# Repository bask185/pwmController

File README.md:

# general purpose IO module with PWM/DCC controller

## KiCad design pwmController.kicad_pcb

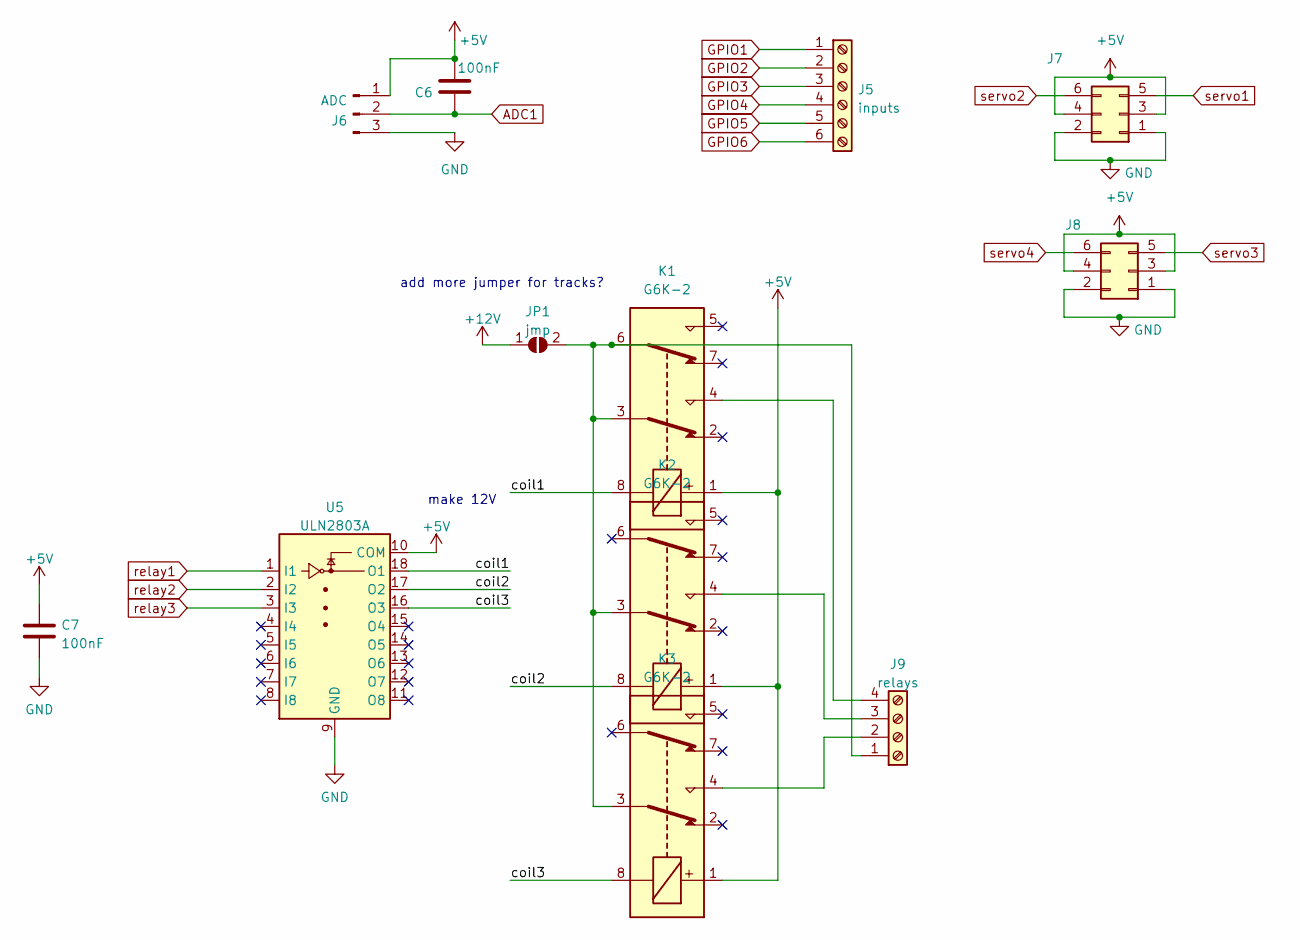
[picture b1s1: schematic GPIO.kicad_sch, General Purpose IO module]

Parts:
C6, C7: 100nF; C_0805_2012Metric
J5: inputs; TerminalBlock_Phoenix_MPT-0,5-8-2.54_1x06_P2.54mm_Horizontal
J6: ADC; PinHeader_1x03_P2.54mm_Vertical
J7, J8: Conn_02x03_Odd_Even; PinHeader_2x03_P2.54mm_Vertical_SMD
J9: relays; TerminalBlock_Phoenix_MKDS-1,5-4-5.08_1x04_P5.08mm_Horizont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
JP1: jmp; SolderJumper-2_P1.3mm_Open_RoundedPad1.0x1.5mm
K1, K2, K3: G6K-2; Relay_DPDT_Omron_G6K-2F-Y; JLCPCB Part# C47190
U5: ULN2803A; SOIC-18W_7.5x11.6mm_P1.27mm

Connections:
+5V: C6.2, C7.1, J6.1, J7.3, J7.4, J8.3, J8.4, K1.1, K2.1, K3.1, U5.10 (COM); also elsewhere on the board
+12V: JP1.1 (A); also elsewhere on the board
/GPIO/coil1: K1.8, U5.18 (O1)
/GPIO/coil2: K2.8, U5.17 (O2)
/GPIO/coil3: K3.8, U5.16 (O3)
ADC1: C6.1, J6.2; also elsewhere on the board
GND: C7.2, J6.3, J7.1, J7.2, J8.1, J8.2, U5.9 (GND); also elsewhere on the board
unnamed: J9.2, K3.4
unnamed: J9.3, K2.4
unnamed: J9.4, K1.4
unnamed: J9.1, JP1.2 (B), K1.3, K1.6, K2.3, K3.3
relay1: U5.1 (I1); also elsewhere on the board
relay2: U5.2 (I2); also elsewhere on the board
relay3: U5.3 (I3); also elsewhere on the board
servo1: J7.5; also elsewhere on the board
servo2: J7.6; also elsewhere on the board
servo3: J8.5; also elsewhere on the board
servo4: J8.6; also elsewhere on the board

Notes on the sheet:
make 12V
add more jumper for tracks?

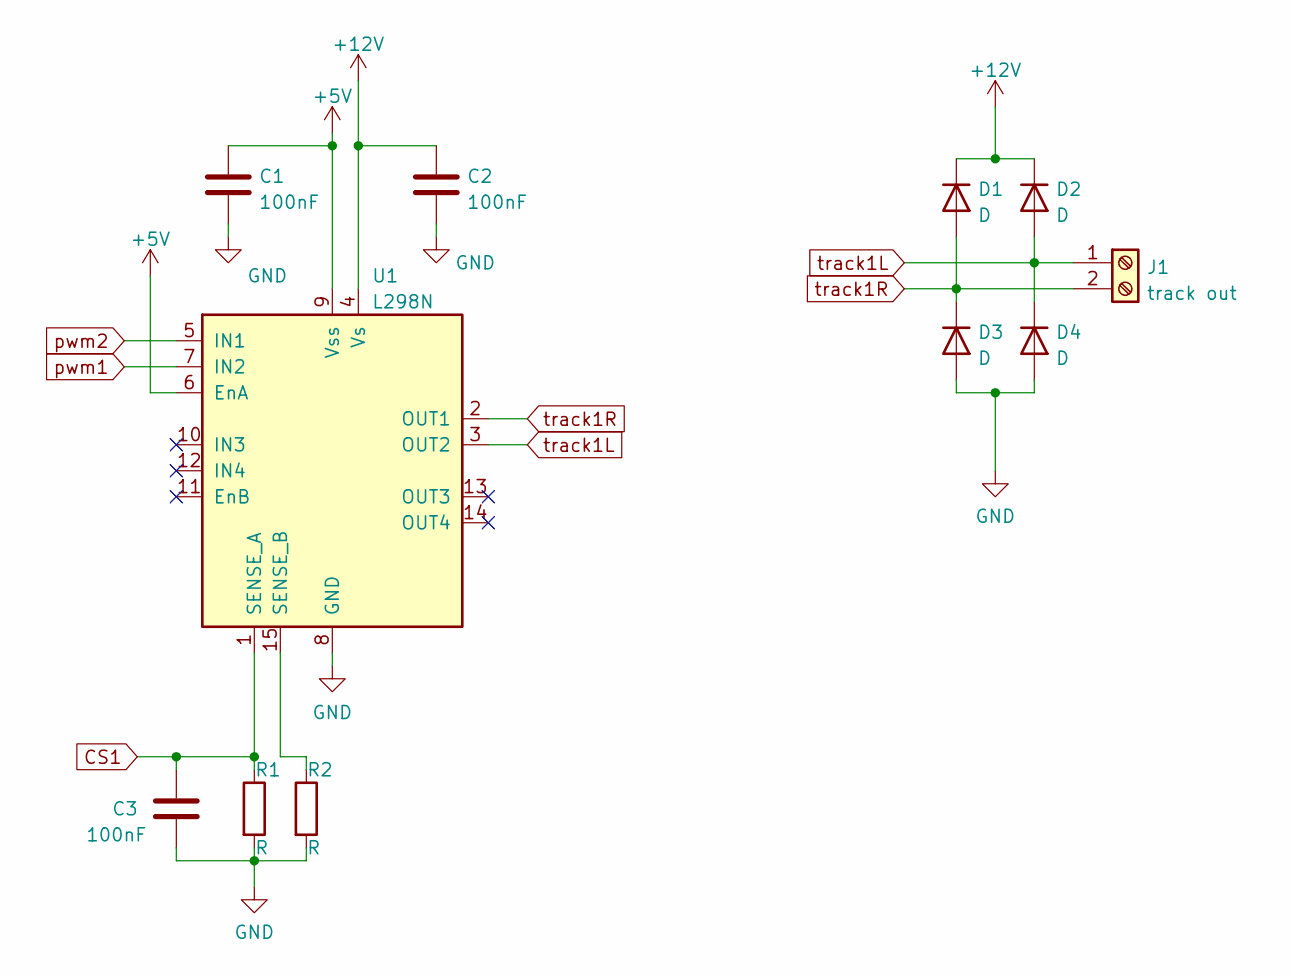
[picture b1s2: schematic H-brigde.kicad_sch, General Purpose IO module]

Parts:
C1, C2, C3: 100nF; C_0805_2012Metric
D1, D2, D3, D4: D; D_1206_3216Metric
J1: track out; TerminalBlock_Phoenix_MKDS-1,5-2-5.08_1x02_P5.08mm_Horizont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
R1, R2: R; R_1206_3216Metric_Pad1.30x1.75mm_HandSolder; JLCPCB Part# C25334
U1: L298N; TO-220-15_P2.54x2.54mm_StaggerOdd_Lead4.58mm_Vertical

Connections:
+5V: C1.1, U1.6 (EnA), U1.9 (Vss); also elsewhere on the board
+12V: C2.1, D1.1 (K), D2.1 (K), U1.4 (Vs); also elsewhere on the board
CS1: C3.2, R1.1, U1.1 (SENSE_A); also elsewhere on the board
GND: C1.2, C2.2, C3.1, D3.2 (A), D4.2 (A), R1.2, R2.2, U1.8 (GND); also elsewhere on the board
unnamed: R2.1, U1.15 (SENSE_B)
pwm1: U1.7 (IN2); also elsewhere on the board
pwm2: U1.5 (IN1); also elsewhere on the board
track1L: D2.2 (A), D4.1 (K), J1.1, U1.3 (OUT2)
track1R: D1.2 (A), D3.1 (K), J1.2, U1.2 (OUT1)

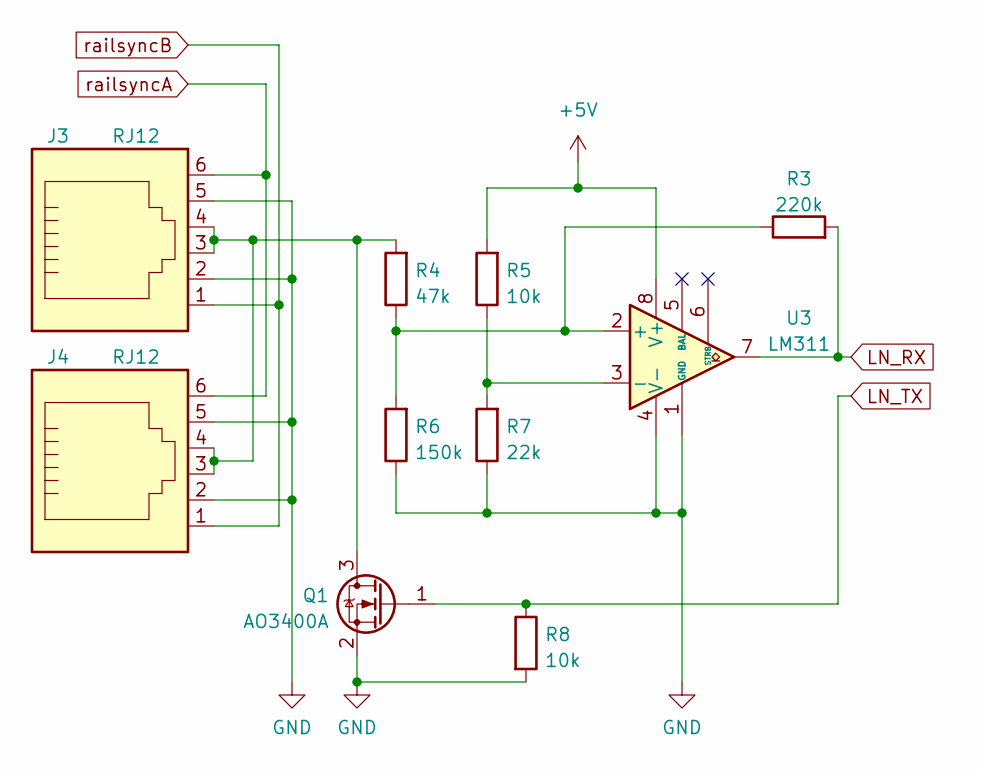
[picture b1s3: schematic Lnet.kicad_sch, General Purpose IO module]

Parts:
J3, J4: RJ12; RJ25_Wayconn_MJEA-660X1_Horizontal; JLCPCB Part# C77859
Q1: AO3400A; SOT-23; JLCPCB Part# C20917
R3: 220k; R_0805_2012Metric_Pad1.20x1.40mm_HandSolder
R4: 47k; R_0805_2012Metric_Pad1.20x1.40mm_HandSolder
R5, R8: 10k; R_0805_2012Metric_Pad1.20x1.40mm_HandSolder
R6: 150k; R_0805_2012Metric_Pad1.20x1.40mm_HandSolder
R7: 22k; R_0805_2012Metric_Pad1.20x1.40mm_HandSolder
U3: LM311; SOP-8_3.9x4.9mm_P1.27mm; JLCPCB Part# C434495

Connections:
+5V: R5.2, U3.8 (V+); also elsewhere on the board
GND: J3.2, J3.5, J4.2, J4.5, Q1.2 (S), R6.1, R7.1, R8.2, U3.1 (GND), U3.4 (V-); also elsewhere on the board
LN_RX: R3.2, U3.7; also elsewhere on the board
LN_TX: Q1.1 (G), R8.1; also elsewhere on the board
unnamed: J3.3, J3.4, J4.3, J4.4, Q1.3 (D), R4.2
unnamed: R3.1, R4.1, R6.2, U3.2 (+)
unnamed: R5.1, R7.2, U3.3 (-)
railsyncA: J3.6, J4.6; also elsewhere on the board
railsyncB: J3.1, J4.1; also elsewhere on the board

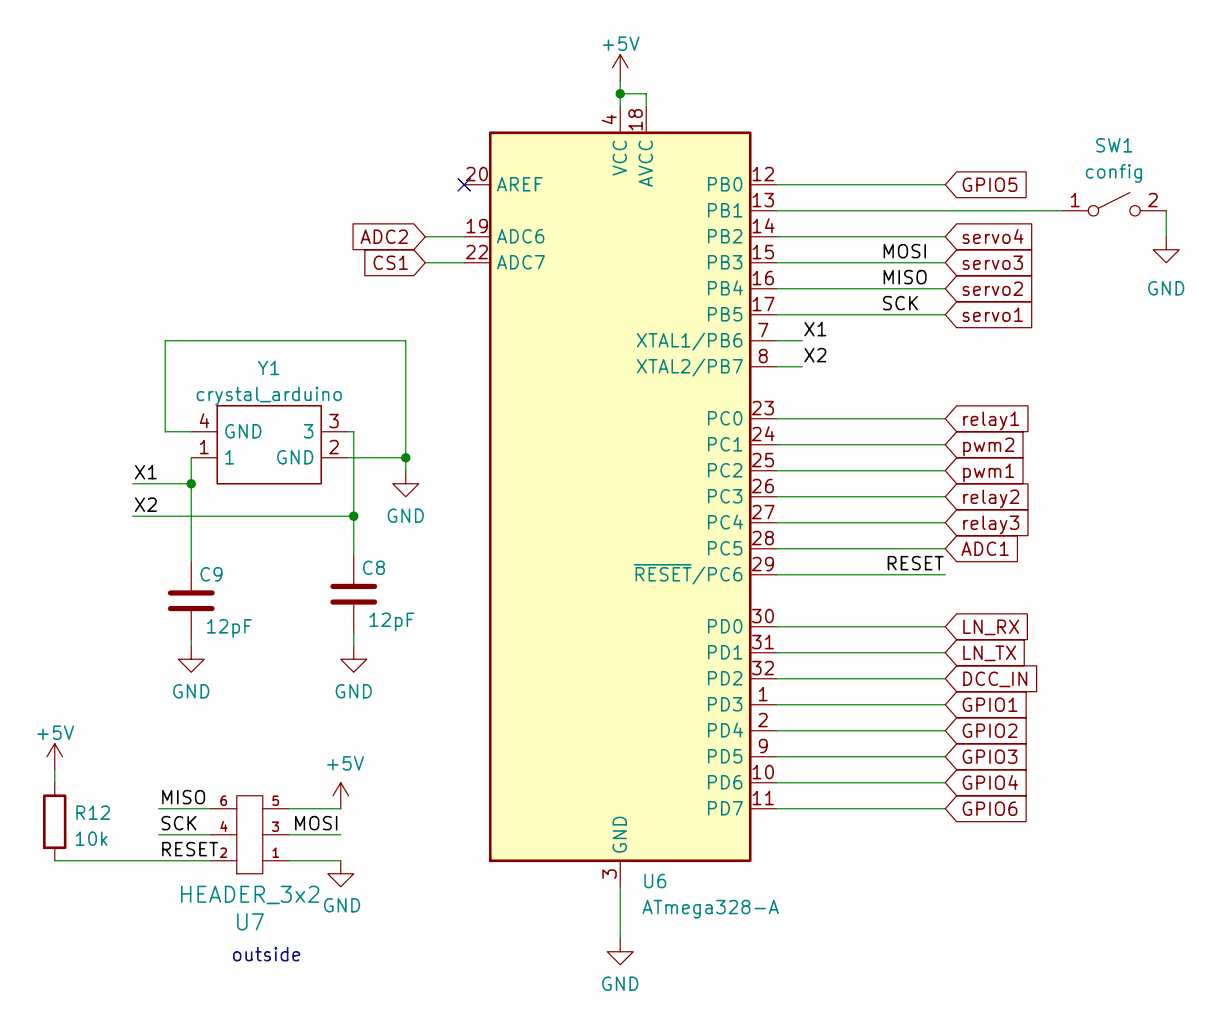
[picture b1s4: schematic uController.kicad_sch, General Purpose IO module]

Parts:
C8, C9: 12pF; C_0603_1608Metric_Pad1.08x0.95mm_HandSolder; JLCPCB Part# C38523
R12: 10k; R_0603_1608Metric_Pad0.98x0.95mm_HandSolder; JLCPCB Part# C25804
SW1: config; SW_SPST_SKQG_WithStem; JLCPCB Part# C318884
U6: ATmega328-A; TQFP-32_7x7mm_P0.8mm; JLCPCB Part# C14877
U7: HEADER_3x2; PinSocket_2x03_P1.27mm_Vertical
Y1: crystal_arduino; JLCPCB Part# C13738

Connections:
+5V: R12.1, U6.4 (VCC), U6.6 (VCC), U6.18 (AVCC), U7.5; also elsewhere on the board
/uController/RESET: R12.2, U6.29 (~RESET/PC6), U7.2
/uController/X1: C9.2, U6.7 (XTAL1/PB6), Y1.1
/uController/X2: C8.2, U6.8 (XTAL2/PB7), Y1.3
ADC1: U6.28 (PC5); also elsewhere on the board
ADC2: U6.19 (ADC6)
CS1: U6.22 (ADC7); also elsewhere on the board
DCC_IN: U6.32 (PD2); also elsewhere on the board
GND: C8.1, C9.1, SW1.2 (B), U6.3 (GND), U6.5 (GND), U6.21 (GND), U7.1, Y1.2 (GND), Y1.4 (GND); also elsewhere on the board
GPIO1: U6.1 (PD3)
GPIO2: U6.2 (PD4)
GPIO3: U6.9 (PD5)
GPIO4: U6.10 (PD6)
GPIO5: U6.12 (PB0)
GPIO6: U6.11 (PD7)
LN_RX: U6.30 (PD0); also elsewhere on the board
LN_TX: U6.31 (PD1); also elsewhere on the board
unnamed: SW1.1 (A), U6.13 (PB1)
pwm1: U6.25 (PC2); also elsewhere on the board
pwm2: U6.24 (PC1); also elsewhere on the board
relay1: U6.23 (PC0); also elsewhere on the board
relay2: U6.26 (PC3); also elsewhere on the board
relay3: U6.27 (PC4); also elsewhere on the board
servo1: U6.17 (PB5), U7.4; also elsewhere on the board
servo2: U6.16 (PB4), U7.6; also elsewhere on the board
servo3: U6.15 (PB3), U7.3; also elsewhere on the board
servo4: U6.14 (PB2); also elsewhere on the board

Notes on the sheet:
outside

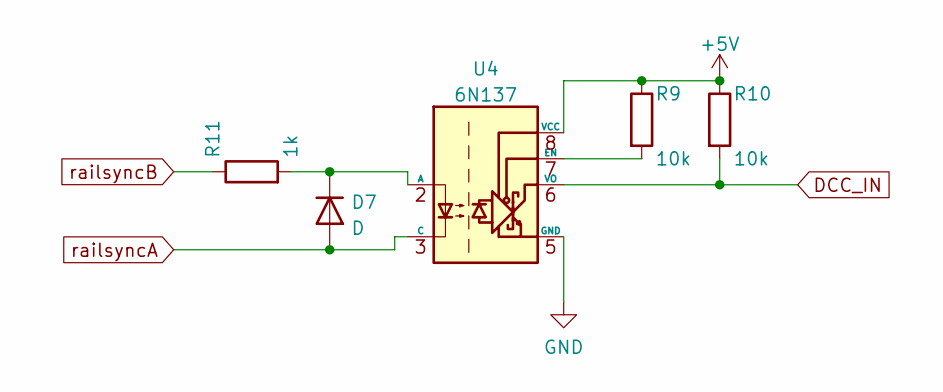
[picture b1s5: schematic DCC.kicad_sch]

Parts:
D7: D; D_1206_3216Metric
R9, R10: 10k; R_0805_2012Metric_Pad1.20x1.40mm_HandSolder; JLCPCB Part# C17414
R11: 1k; R_0805_2012Metric_Pad1.20x1.40mm_HandSolder; JLCPCB Part# C17513
U4: 6N137; SOP-8_6.62x9.15mm_P2.54mm; JLCPCB Part# C110020

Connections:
+5V: R9.1, R10.1, U4.8 (VCC); also elsewhere on the board
DCC_IN: R10.2, U4.6 (VO); also elsewhere on the board
GND: U4.5 (GND); also elsewhere on the board
unnamed: D7.1 (K), R11.2, U4.2 (A)
unnamed: R9.2, U4.7 (EN)
railsyncA: D7.2 (A), U4.3 (C); also elsewhere on the board
railsyncB: R11.1; also elsewhere on the board

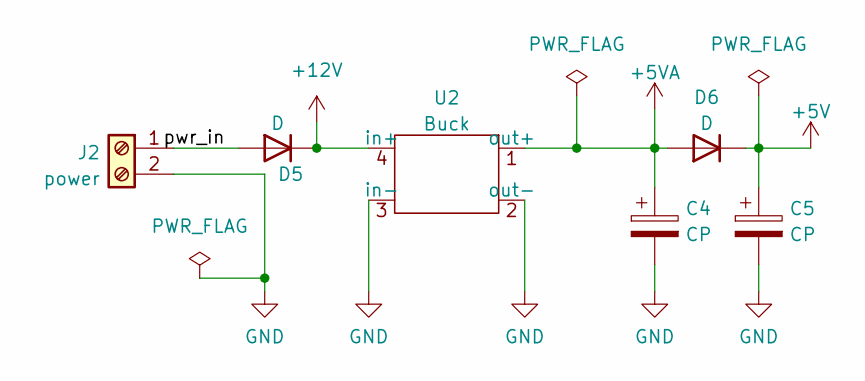
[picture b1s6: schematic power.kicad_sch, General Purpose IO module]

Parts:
C4, C5: CP; CP_Elec_6.3x7.7; JLCPCB Part# C125975
D5, D6: D; D_1206_3216Metric
J2: power; TerminalBlock_Phoenix_MKDS-1,5-2-5.08_1x02_P5.08mm_Horizont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
U2: Buck

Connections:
+5V: C5.1, D6.1 (K); also elsewhere on the board
+5VA: C4.1, D6.2 (A), U2.1 (out+)
+12V: D5.1 (K), U2.4 (in+); also elsewhere on the board
/power/pwr_in: D5.2 (A), J2.1
GND: C4.2, C5.2, J2.2, U2.2 (out-), U2.3 (in-); also elsewhere on the board

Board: 2 copper layers, 50 parts (1 on the bottom side), 40 nets, no tracks yet.

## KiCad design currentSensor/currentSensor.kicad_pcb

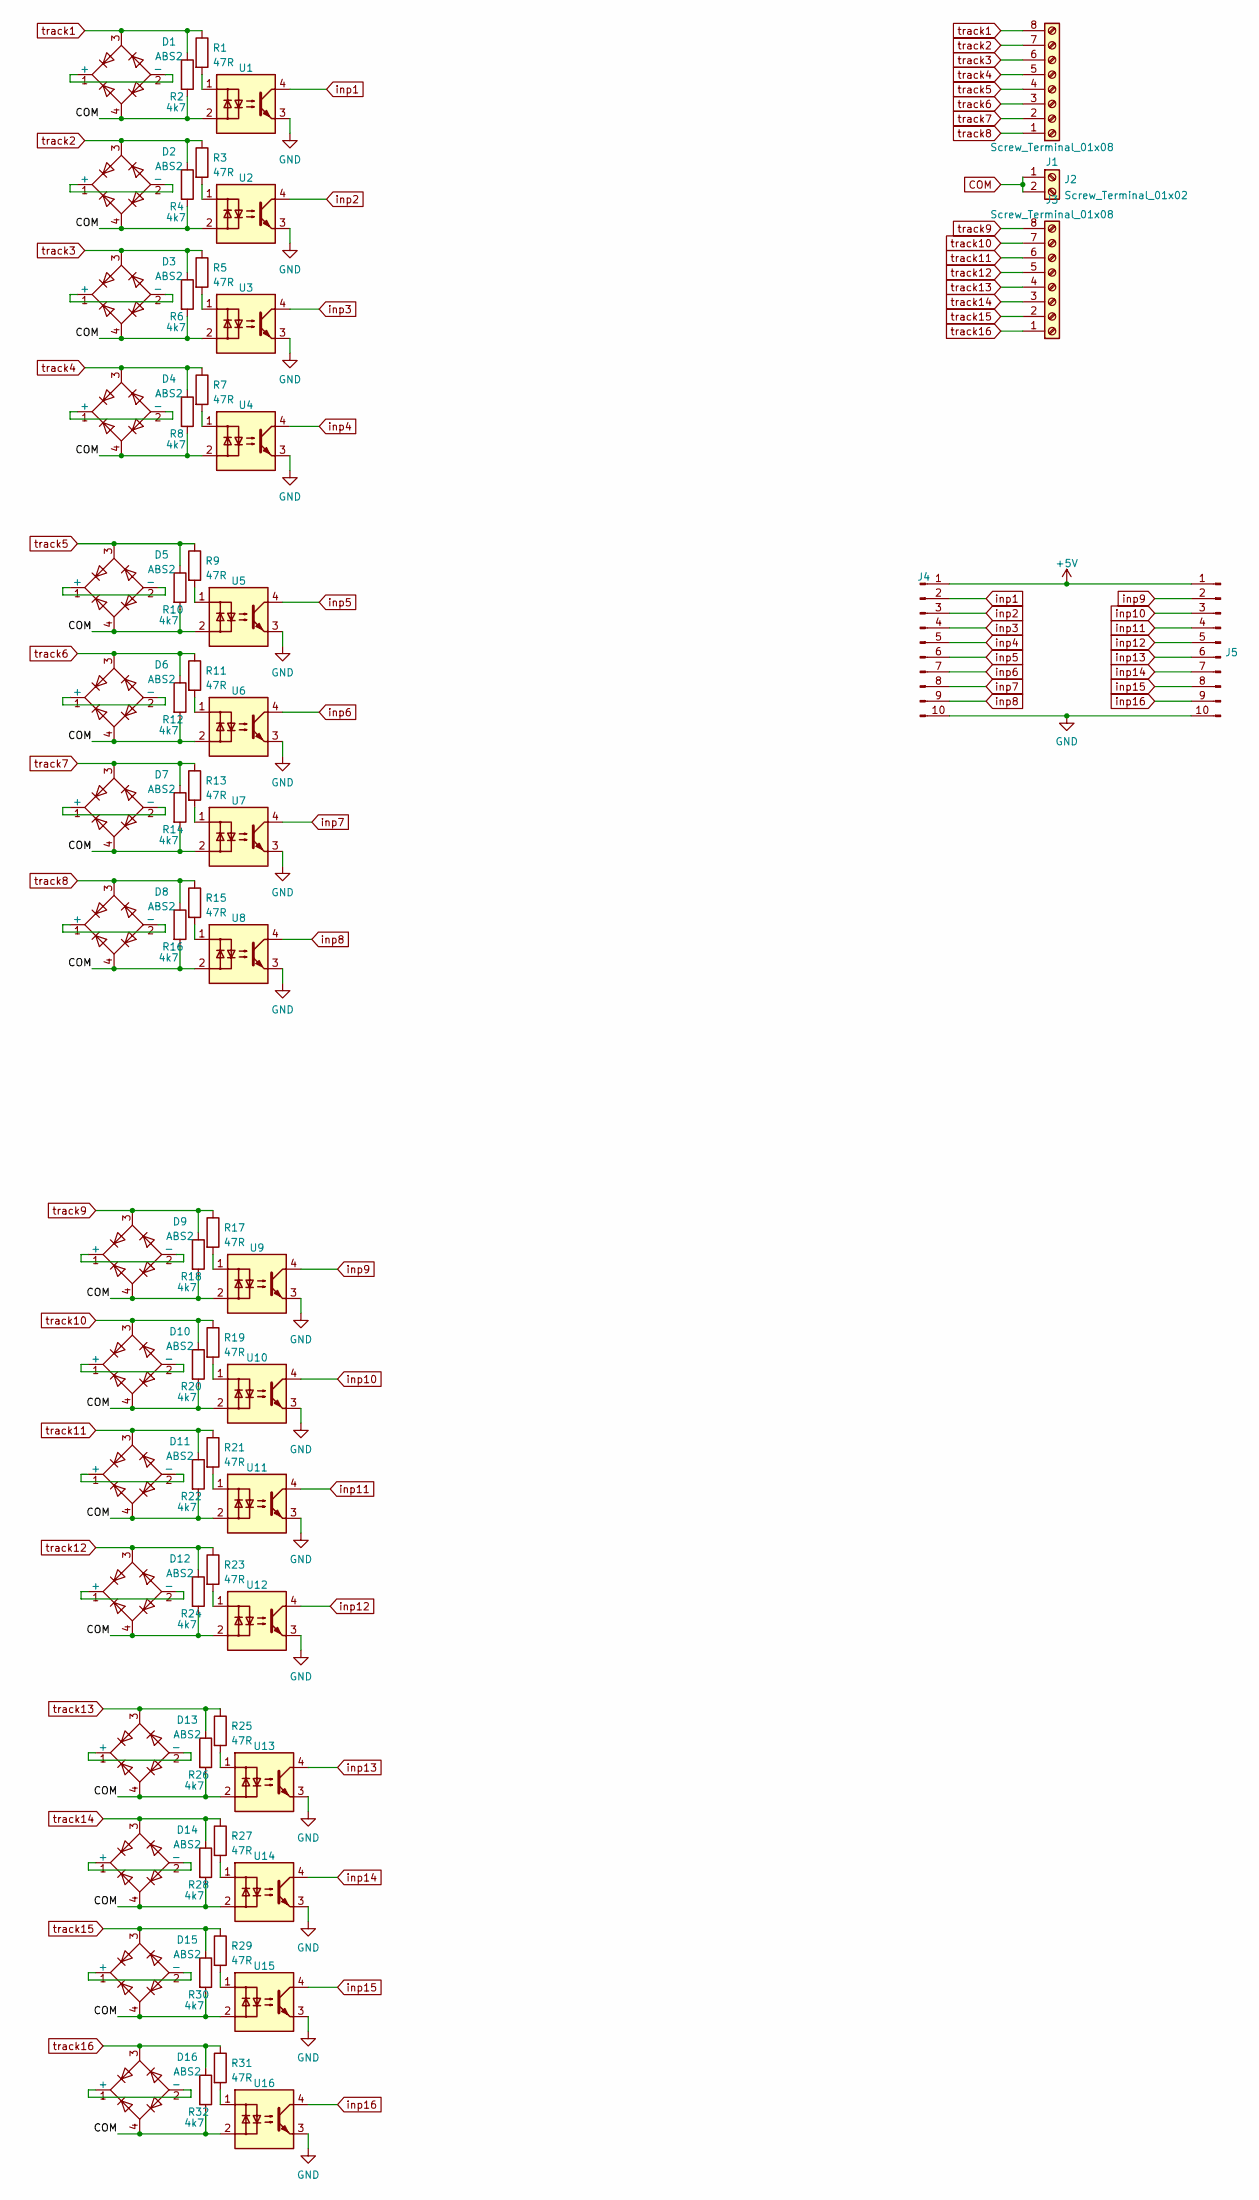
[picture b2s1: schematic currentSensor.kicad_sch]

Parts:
D1, D2, D3, D4, D5, D6, D7, D8, D9, D10, D11, D12, D13, D14, D15, D16: ABS2; Diode_Bridge_Diotec_ABS; JLCPCB Part# C123897
J1, J3: Screw_Terminal_01x08; TerminalBlock_Phoenix_MKDS-1,5-8-5.08_1x08_P5.08mm_Horizont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
J2: Screw_Terminal_01x02; TerminalBlock_Phoenix_MKDS-1,5-2-5.08_1x02_P5.08mm_Horizont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
J4, J5: Conn_01x10_Male; PinHeader_1x10_P2.54mm_Horizontal
R1, R3, R5, R7, R9, R11, R13, R15, R17, R19, R21, R23, R25, R27, R29, R31: 47R; R_0805_2012Metric_Pad1.20x1.40mm_HandSolder; JLCPCB Part# C17714
R2, R4, R6, R8, R10, R12, R14, R16, R18, R20, R22, R24, R26, R28, R30, R32: 4k7; R_0805_2012Metric_Pad1.20x1.40mm_HandSolder; JLCPCB Part# C17673
U1, U2, U3, U4, U5, U6, U7, U8, U9, U10, U11, U12, U13, U14, U15, U16: SFH6206-2T; SMDIP-4_W9.53mm_Clearance8mm; JLCPCB Part# C143678

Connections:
+5V: J4.1, J5.1
COM: D1.4, D2.4, D3.4, D4.4, D5.4, D6.4, D7.4, D8.4, D9.4, D10.4, D11.4, D12.4, D13.4, D14.4, D15.4, D16.4, J2.1, J2.2, R2.2, R4.2, R6.2, R8.2, R10.2, R12.2, R14.2, R16.2, R18.2, R20.2, R22.2, R24.2, R26.2, R28.2, R30.2, R32.2, U1.2, U2.2, U3.2, U4.2, U5.2, U6.2, U7.2, U8.2, U9.2, U10.2, U11.2, U12.2, U13.2, U14.2, U15.2, U16.2
GND: J4.10, J5.10, U1.3, U2.3, U3.3, U4.3, U5.3, U6.3, U7.3, U8.3, U9.3, U10.3, U11.3, U12.3, U13.3, U14.3, U15.3, U16.3
unnamed: D1.1 (+), D1.2 (-)
unnamed: D2.1 (+), D2.2 (-)
unnamed: D3.1 (+), D3.2 (-)
unnamed: D4.1 (+), D4.2 (-)
unnamed: D5.1 (+), D5.2 (-)
unnamed: D6.1 (+), D6.2 (-)
unnamed: D7.1 (+), D7.2 (-)
unnamed: D8.1 (+), D8.2 (-)
unnamed: D9.1 (+), D9.2 (-)
unnamed: D10.1 (+), D10.2 (-)
unnamed: D11.1 (+), D11.2 (-)
unnamed: D12.1 (+), D12.2 (-)
unnamed: D13.1 (+), D13.2 (-)
unnamed: D14.1 (+), D14.2 (-)
unnamed: D15.1 (+), D15.2 (-)
unnamed: D16.1 (+), D16.2 (-)
unnamed: R1.2, U1.1
unnamed: R3.2, U2.1
unnamed: R5.2, U3.1
unnamed: R7.2, U4.1
unnamed: R9.2, U5.1
unnamed: R11.2, U6.1
unnamed: R13.2, U7.1
unnamed: R15.2, U8.1
unnamed: R17.2, U9.1
unnamed: R19.2, U10.1
unnamed: R21.2, U11.1
unnamed: R23.2, U12.1
unnamed: R25.2, U13.1
unnamed: R27.2, U14.1
unnamed: R29.2, U15.1
unnamed: R31.2, U16.1
inp1: J4.2, U1.4
inp2: J4.3, U2.4
inp3: J4.4, U3.4
inp4: J4.5, U4.4
inp5: J4.6, U5.4
inp6: J4.7, U6.4
inp7: J4.8, U7.4
inp8: J4.9, U8.4
inp9: J5.2, U9.4
inp10: J5.3, U10.4
inp11: J5.4, U11.4
inp12: J5.5, U12.4
inp13: J5.6, U13.4
inp14: J5.7, U14.4
inp15: J5.8, U15.4
inp16: J5.9, U16.4
track1: D1.3, J1.8, R1.1, R2.1
track2: D2.3, J1.7, R3.1, R4.1
track3: D3.3, J1.6, R5.1, R6.1
track4: D4.3, J1.5, R7.1, R8.1
track5: D5.3, J1.4, R9.1, R10.1
track6: D6.3, J1.3, R11.1, R12.1
track7: D7.3, J1.2, R13.1, R14.1
track8: D8.3, J1.1, R15.1, R16.1
track9: D9.3, J3.8, R17.1, R18.1
track10: D10.3, J3.7, R19.1, R20.1
track11: D11.3, J3.6, R21.1, R22.1
track12: D12.3, J3.5, R23.1, R24.1
track13: D13.3, J3.4, R25.1, R26.1
track14: D14.3, J3.3, R27.1, R28.1
track15: D15.3, J3.2, R29.1, R30.1
track16: D16.3, J3.1, R31.1, R32.1

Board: 2 copper layers, 69 parts (0 on the bottom side), 67 nets, no tracks yet.

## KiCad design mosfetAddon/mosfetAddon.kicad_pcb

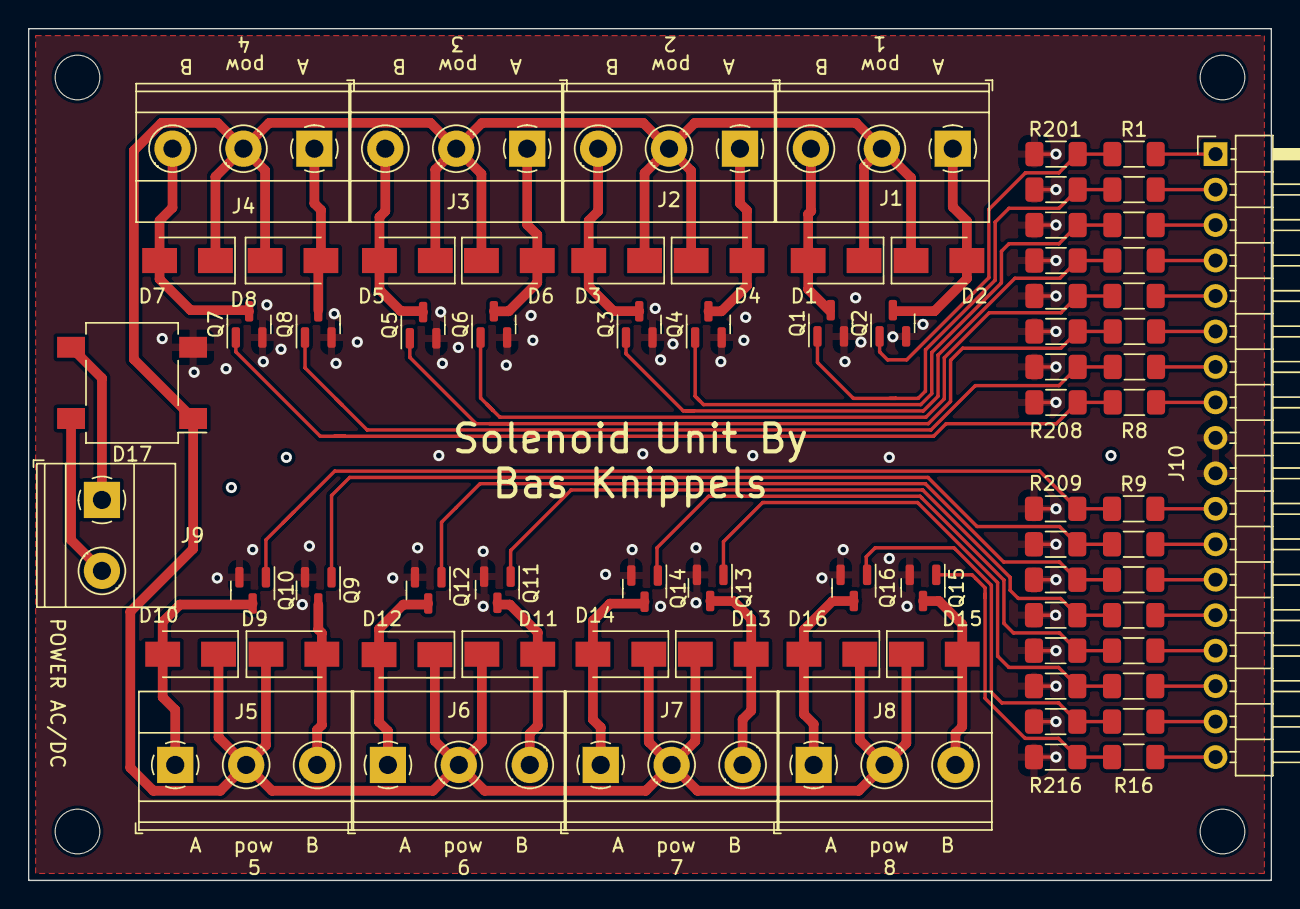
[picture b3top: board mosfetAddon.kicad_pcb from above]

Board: 2 copper layers, 89.0 x 61.0 mm, 75 parts (0 on the bottom side), 52 nets.

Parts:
D1, D2, D3, D4, D5, D6, D7, D8, D9, D10, D11, D12, D13, D14, D15, D16: D; D_SMA
D17: D_Bridge_+-AA; Diode_Bridge_Diotec_SO-DIL-Slim
J1, J2, J3, J4, J5, J6, J7, J8: coil; TerminalBlock_Phoenix_MKDS-1,5-3-5.08_1x03_P5.08mm_Horizont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
J9: pow; TerminalBlock_Phoenix_MKDS-1,5-2-5.08_1x02_P5.08mm_Horizont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
J10: Conn_01x18_Male; PinHeader_1x18_P2.54mm_Horizontal
Q1, Q2, Q3, Q4, Q5, Q6, Q7, Q8, Q9, Q10, Q11, Q12, Q13, Q14, Q15, Q16: AO3400A; SOT-23
R1, R2, R3, R4, R5, R6, R7, R8, R9, R10, R11, R12, R13, R14, R15, R16: 22R; R_1206_3216Metric_Pad1.30x1.75mm_HandSolder
R201, R202, R203, R204, R205, R206, R207, R208, R209, R210, R211, R212, R213, R214, R215, R216: 10k; R_1206_3216Metric_Pad1.30x1.75mm_HandSolder

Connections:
GND: D17.2 (-), J10.9, J10.10, Q1.2 (S), Q2.2 (S), Q3.2 (S), Q4.2 (S), Q5.2 (S), Q6.2 (S), Q7.2 (S), Q8.2 (S), Q9.2 (S), Q10.2 (S), Q11.2 (S), Q12.2 (S), Q13.2 (S), Q14.2 (S), Q15.2 (S), Q16.2 (S), R201.1, R202.1, R203.1, R204.1, R205.1, R206.1, R207.1, R208.1, R209.1, R210.1, R211.1, R212.1, R213.1, R214.1, R215.1, R216.1
unnamed: D17.3, J9.1
unnamed: D17.4, J9.2
unnamed: Q2.1 (G), R1.2, R201.2
unnamed: Q1.1 (G), R2.2, R202.2
unnamed: Q4.1 (G), R3.2, R203.2
unnamed: Q3.1 (G), R4.2, R204.2
unnamed: Q6.1 (G), R5.2, R205.2
unnamed: Q5.1 (G), R6.2, R206.2
unnamed: Q8.1 (G), R7.2, R207.2
unnamed: Q7.1 (G), R8.2, R208.2
unnamed: Q10.1 (G), R9.2, R209.2
unnamed: Q9.1 (G), R10.2, R210.2
unnamed: Q12.1 (G), R11.2, R211.2
unnamed: Q11.1 (G), R12.2, R212.2
unnamed: Q14.1 (G), R13.2, R213.2
unnamed: Q13.1 (G), R14.2, R214.2
unnamed: Q16.1 (G), R15.2, R215.2
unnamed: Q15.1 (G), R16.2, R216.2
coil1L: D1.2 (A), J1.3, Q1.3 (D)
coil1R: D2.2 (A), J1.1, Q2.3 (D)
coil2L: D3.2 (A), J2.3, Q3.3 (D)
coil2R: D4.2 (A), J2.1, Q4.3 (D)
coil3L: D5.2 (A), J3.3, Q5.3 (D)
coil3R: D6.2 (A), J3.1, Q6.3 (D)
coil4L: D7.2 (A), J4.3, Q7.3 (D)
coil4R: D8.2 (A), J4.1, Q8.3 (D)
coil5L: D9.2 (A), J5.3, Q9.3 (D)
coil5R: D10.2 (A), J5.1, Q10.3 (D)
coil6L: D11.2 (A), J6.3, Q11.3 (D)
coil6R: D12.2 (A), J6.1, Q12.3 (D)
coil7L: D13.2 (A), J7.3, Q13.3 (D)
coil7R: D14.2 (A), J7.1, Q14.3 (D)
coil8L: D15.2 (A), J8.3, Q15.3 (D)
coil8R: D16.2 (A), J8.1, Q16.3 (D)
gate1L: J10.2, R2.1
gate1R: J10.1, R1.1
gate2L: J10.4, R4.1
gate2R: J10.3, R3.1
gate3L: J10.6, R6.1
gate3R: J10.5, R5.1
gate4L: J10.8, R8.1
gate4R: J10.7, R7.1
gate5L: J10.12, R10.1
gate5R: J10.11, R9.1
gate6L: J10.14, R12.1
gate6R: J10.13, R11.1
gate7L: J10.16, R14.1
gate7R: J10.15, R13.1
gate8L: J10.18, R16.1
gate8R: J10.17, R15.1
pow: D1.1 (K), D2.1 (K), D3.1 (K), D4.1 (K), D5.1 (K), D6.1 (K), D7.1 (K), D8.1 (K), D9.1 (K), D10.1 (K), D11.1 (K), D12.1 (K), D13.1 (K), D14.1 (K), D15.1 (K), D16.1 (K), D17.1 (+), J1.2, J2.2, J3.2, J4.2, J5.2, J6.2, J7.2, J8.2

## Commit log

2022-10-09 reading MCP works button debouncing works button reading works processing buttons, untested (need hardware for this) servoSweep works adjusting servos does not work (motors will not detach after an a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
2022-10-10 may of may not have fixed the adjusting of servo's
2022-10-10 may have the relays working. Should be tested with an LED as soon as the IO extender arrives. Also need to solder pin1 (A0) to 5V due to address conflict with mcp23017
2022-10-10 made drastic changes to PCB design. I added 2nd Rj12 connector, side by side connectors, 2 analog inpouts and 2nd channel of H bridge is commissioned
2022-10-10 finetuning of servo's work, but in one direction a bit.. choppy. I don't know why exactly. I am thinking to utilize the multimaus knob for this purpose. The recording and playing also work. The servo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
    I only have to solder the first motor
2022-10-11 divided the schematic in several sheets.
    PCB needs to be redrawn because the link between components is gone
2022-10-11 added valueable comments with things to do and listed ideas
2022-10-12 changed PCB layout. I want to change more
2022-10-12 redone the switch connectors to accomodate a current sense print. Rearranged parts and updated silk texts to be 50% of their original size
2022-10-14 I have a problem that I lose the links between symbols and footprints. I want to add a spst switch to connect the bus' voltage to the main power
2022-10-19 added mosfet addon
2022-10-24 about to redo the PCB with an atmega 2560 instead. This will eliminate the need for 2 IO extenders and gives me the extra serial interface which I need. I also lack IO on the 328p
2022-10-25 relay are working but one. Multimaus control with IO sometimes seem buggy, but works in general. In worst case you have to press the same button another time.
    Storing and saving program also works. Only the channel selection does not seem to work properly.
2022-10-26 added something to debug the channel buttons
2022-10-29 checkout to other version
2022-10-30 added some changed to the current sensor. There also seems a bug with the mcp23017. I suspect the chip itself may be damaged. Not all pins are at 5V
2022-12-31 about to make new branch for control panel usage
2023-01-01 commit for checkout. Added some code to handle combined input/output but in retrospect it is not neededy
2023-01-01 added missing files
2023-01-01 commit for push. Code cannot yet compile because nx.cpp does not have the input objects.
2023-01-01 ditched the Nx files. I felt it was not needed
2023-01-02 altered the code drastically and made a new PCB. PCB is still much work.
    I finally fixed that issue where loco functions and speed were not serviced to the multimaus clients.
    The Nx code also has been succesfully tested using the monitor.
    MCP bug also has been solded. The bug was in assembleIO.py
2023-01-02 The maus is now also serviced with point information. It is however hollow feedback sending all point straight
2023-01-03 added missing schematics
2023-01-03 replaced the atmega2560 by an stm32
2023-01-14 added and changed alot of MCP code. Now re testing the inputs.
2023-01-16 added separate HAL files for NX and empty files for the MCP23017. They need filling in for read and write registers
2023-01-16 filled in 2 functions for the mcp23017. Yet to add EEPROM functions
2023-01-16 added i2c libaries
2023-01-16 nx files are sorta ready for testing purposed. A new branch must be made
2023-01-16 commit for new branch
2023-01-16 All LEDs work well now. I do want to add a little more thingies.
2023-01-16 Koen's version is working properly. Remaining defective LEDs are replaced and resoldered. All combinations work properly now. I only need to work on the playing recording part and the servo for the d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
2023-01-21 added code for recording/playing. added code for decoupler both are untested
2023-01-28 Code for recording and playing has been bested throroughly. All servo's are tested when used in with Nx switchting. Going to make a release
2023-02-01 added routes file and heavily refactored to more OOP style. Code does not yet work I must figure how to link the point and button objects. I may want to relocate the routes to the ino file instead
2023-02-01 code made compilable. Setting routes n all should work. However processing the buttons is yet to be made
2023-02-01 minor commit for push
2023-02-04 added i2c files for board2board communication
2023-02-04 added some i2c code but it needs altering. A slave must not run Xnet code, when he is I2C master A slave also must not run Nx code. It must continously debounce it's inputs and send all 15 to the the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
2023-02-05 missing Nx files. I deleted them earlier for some reason. They may be on work PC still.
2023-02-05 project compiles, stil need nx files though.
    I2C code is added, should be tested
2023-02-05 added some more code for I2C. I could use a different method for debouncing. I also need to filter out leds somehow
2023-02-06 added the Nx files
2023-02-06 Code is compilable and is ready for testing. I2C should be tested first. A separate version is made for slave operation. The point and NxButton arrays should be relocated to Routes.h so all project u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
2023-02-06 added i2c task instruction, added GPIO array and added a few comments. In big lines this code may actually work
2023-02-07 redid this project. I want to use an atmega328 so I ditched some IO. I retained 4 servo, 1 H-bridge (should make it double), 3 relays, 6 GPIO, 1 potentiometer and loconet interface. And I still have 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
2023-02-07 added 2 missing cheamtic sheets and deleted obsolete sheets
